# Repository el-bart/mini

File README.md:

mini
====

repo for mini-projects (one-filers, etc...).

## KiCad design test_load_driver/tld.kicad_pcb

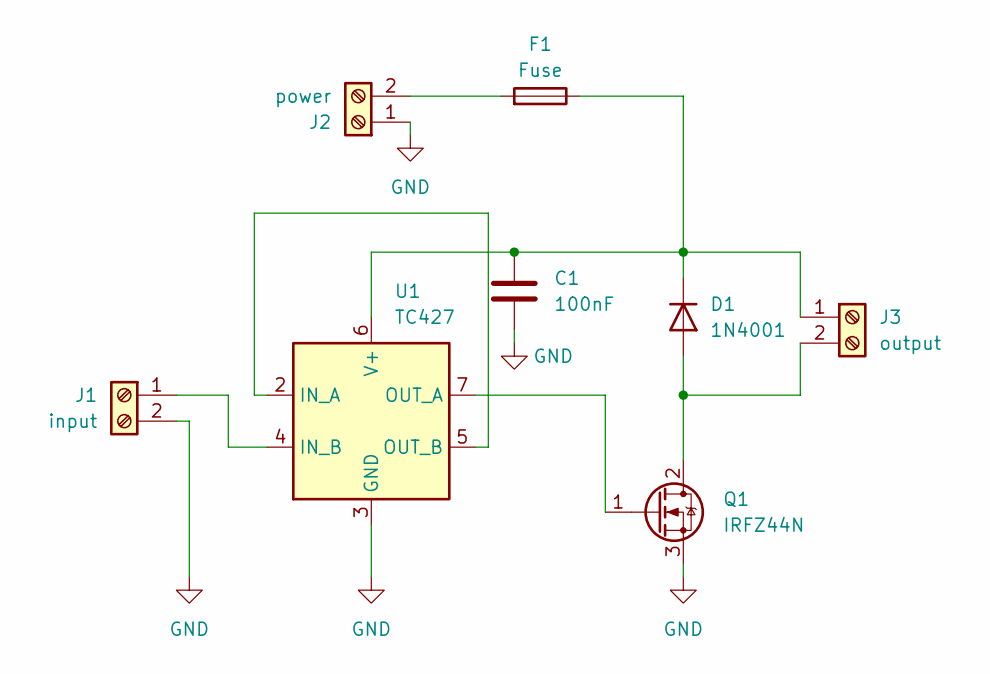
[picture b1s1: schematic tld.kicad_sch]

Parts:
C1: 100nF; C_Rect_L9.0mm_W2.5mm_P7.50mm_MKT
D1: 1N4001; D_DO-41_SOD81_P10.16mm_Horizontal
F1: Fuse; Fuseholder_Cylinder-5x20mm_Schurter_0031_8201_Horizontal_Op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
J1: input; PinHeader_1x02_P2.54mm_Vertical
J2: power; PinHeader_1x02_P2.54mm_Vertical
J3: output; PinHeader_1x02_P2.54mm_Vertical
Q1: IRFZ44N; TO-220-3_Vertical
U1: TC427; DIP-8_W7.62mm

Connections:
GND: C1.2, J1.2, J2.1, Q1.3 (S), U1.3 (GND)
unnamed: D1.2 (A), J3.2, Q1.2 (D)
unnamed: C1.1, D1.1 (K), F1.1, J3.1, U1.6 (V+)
unnamed: J1.1, U1.4 (IN_B)
unnamed: F1.2, J2.2
unnamed: Q1.1 (G), U1.7 (OUT_A)
unnamed: U1.2 (IN_A), U1.5 (OUT_B)

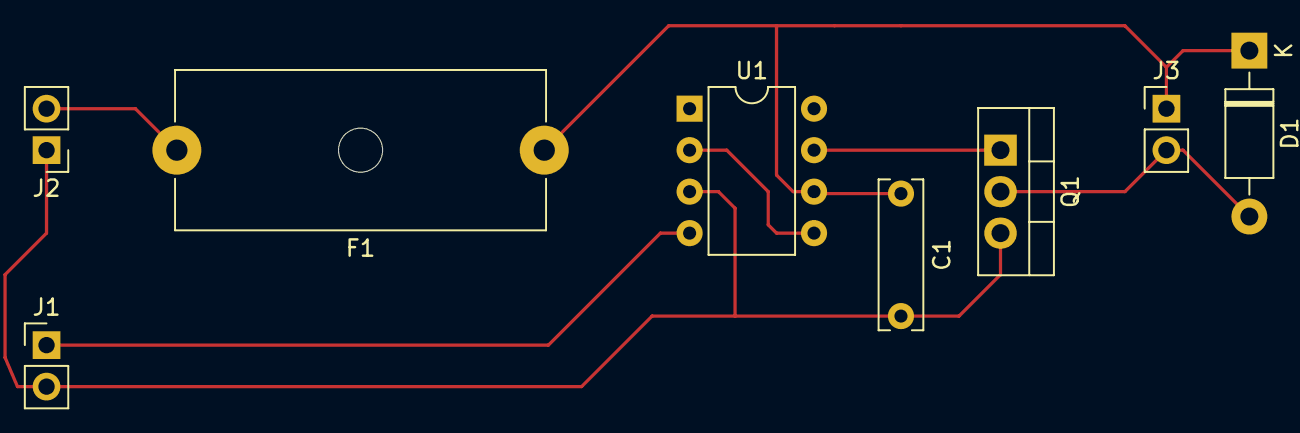
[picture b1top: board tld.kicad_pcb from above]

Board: 2 copper layers, 8 parts (0 on the bottom side), 7 nets.

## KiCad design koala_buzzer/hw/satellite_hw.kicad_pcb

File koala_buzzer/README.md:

# koala buzzer

fix board for child toy.
a buzzer, that lost controller board.

this uses PCB and other elements from [toy satellite model](https://github.com/el-bart/toy_satellite_model) project.
SW undergo minimal changes.

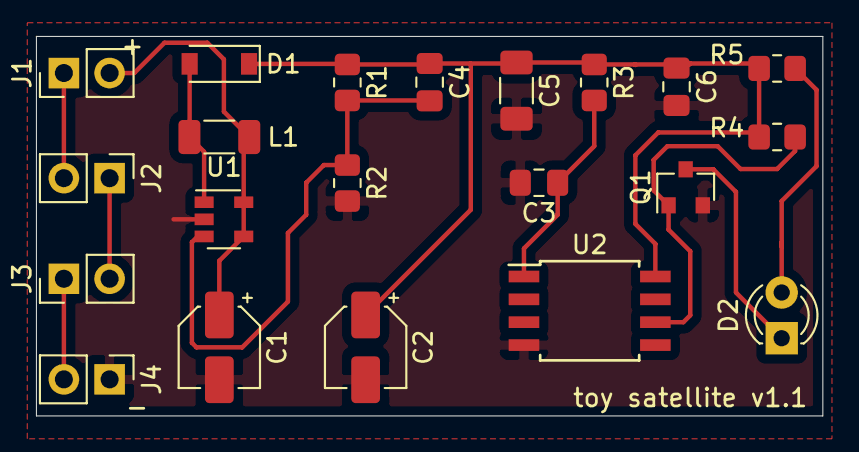
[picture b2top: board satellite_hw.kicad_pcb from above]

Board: 2 copper layers, 43.7 x 21.1 mm, 21 parts (0 on the bottom side), 12 nets.

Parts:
C1: 10µF; CP_Elec_4x3.9
C2: 1µF; CP_Elec_4x3.9
C3: 4.7nF; C_0805_2012Metric_Pad1.18x1.45mm_HandSolder
C4: 10pF; C_0805_2012Metric_Pad1.18x1.45mm_HandSolder
C5: 100nF; C_1206_3216Metric_Pad1.33x1.80mm_HandSolder
C6: 10nF; C_0805_2012Metric_Pad1.18x1.45mm_HandSolder
D1: D_Schottky; D_SOD-123
D2: red; LED_D3.0mm
J1: solar 1; PinHeader_1x02_P2.54mm_Vertical
J2: solar 2; PinHeader_1x02_P2.54mm_Vertical
J3: solar 3; PinHeader_1x02_P2.54mm_Vertical
J4: solar 4; PinHeader_1x02_P2.54mm_Vertical
L1: 10µH; L_1206_3216Metric_Pad1.22x1.90mm_HandSolder
Q1: 2N7002; SOT-23
R1: 680k; R_0805_2012Metric_Pad1.20x1.40mm_HandSolder
R2: 220k; R_0805_2012Metric_Pad1.20x1.40mm_HandSolder
R3, R4: 10k; R_0805_2012Metric_Pad1.20x1.40mm_HandSolder
R5: 470R; R_0805_2012Metric_Pad1.20x1.40mm_HandSolder
U1: AP3015; SOT-23-5
U2: ATtiny13-20SU; SOIJ-8_5.3x5.3mm_P1.27mm

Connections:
+5V: C2.1, C4.1, C5.1, C6.1, D1.1, R1.1, R3.1, R4.1, R5.1, U2.8
GNDD: C1.2, C2.2, C3.2, C5.2, C6.2, J4.1, Q1.2, R2.2, U1.2, U2.4
unnamed: C3.1, R3.2, U2.1
unnamed: C4.2, R1.2, R2.1, U1.3
unnamed: D1.2, L1.2, U1.1
unnamed: D2.1, Q1.3
unnamed: D2.2, R5.2
unnamed: J1.1, J2.2
unnamed: J2.1, J3.2
unnamed: J3.1, J4.2
unnamed: Q1.1, R4.2, U2.6
VCC: C1.1, J1.2, L1.1, U1.4, U1.5

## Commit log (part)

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2025-12-07 LED simplified
2025-12-07 watchdog set yo 8s
2025-12-07 back to 120ms
2025-12-07 adjsutements after changing namespaces
2025-12-07 SwPWM draft
2025-12-07 PoC with 50% duty cycle
2025-12-07 removed unused param
2025-12-07 helper scritp for computing gamma-correction LUT for AVR
2025-12-07 added fade in and out to main
2025-12-07 fade in and out impl. for LED::State + some compile-time constants to play with
2025-12-07 renamed LUT generator + added nicer formatting
2025-12-07 added custom cycle for on/off-s
2025-12-07 cycles are now generated using rand()
2025-12-08 added code generation for LUT
2025-12-08 using generated code now
2025-12-08 added PRNG seeded based on EEPROM, to save some entropy
2025-12-08 keeping seed as unsigned to avoid flipping signed values
2025-12-09 there's s macro for wairing for write to complete
2025-12-09 added C++ compliant number to pointer conversion
2025-12-09 working read-write example
2025-12-09 compile / flash / read hex scripts
2025-12-09 * fixed PRNG state saving * removed test / PoC code for EEPROM from main()
2025-12-09 moved compile time constant to a place where it's actually used
2025-12-09 more cannonical init
2025-12-21 xmass light mounts on a balkony - 3D SDK
2025-12-21 project description
2025-12-21 PET-G/waterproof
2025-12-21 corner hook design
2025-12-21 printing 10x at a time
2025-12-21 moved corner-hook-specific param to the model file
2025-12-21 prototype for a balcony hook
2025-12-21 6x books
2025-12-21 added rim around for some extra stiffness
2025-12-21 removed bottom notch
2025-12-21 adjusted printing parameters for easier printing
2025-12-29 added description of the repo
2025-12-29 3D SDK for camera mount
2025-12-29 1st draft of the mount base
2025-12-29 adjusted sizes, and rotated to for print orientation
2025-12-29 0.3mm layer height, as we're mor interested in speat than precision here
2025-12-29 added camera holder itself
2025-12-29 added Wayland forwardinf for steam (WIP)
2025-12-29 added missing libs for Vulkan and Mesa
2025-12-29 * added wayland forwarding * added steam flags to run non-sandboxed CEF
2025-12-29 steam bumped to debian:13 + added missing tools for Vulkan
2025-12-29 3D SDK for multiple marker holders for whiteboard
2025-12-29 multi-marker holder
2025-12-29 added some nice touches to make print easier to handle
2025-12-29 bed temperature down to 60°C for PLA/Silk
2026-01-01 added Xwayland for image
2026-01-01 WIP for Wayland
2026-01-01 removed Wayland testing code
2026-01-01 Wayland note
2026-01-01 fixed comment
2026-01-10 3D SDK for digital hourglass
2026-01-10 trigger board enc for USB-C added as a helper model
2026-01-10 added hourglass box
2026-01-11 draft of CubicSDR
2026-01-11 WIP...
2026-01-11 fixed SDR device access
2026-01-11 fixed path to dockerfile, when not running from a local dir
2026-01-11 3D SDK for AVT's dusk sensor
2026-01-11 USB-C trigger board
2026-01-11 dusk switch box
2026-01-11 added LED support strip, to make connection more firm (yes, it's not part of the set, but it's how my kids use it - so there u have it... ;))
2026-01-12 3D SDK for toy rocket cone
2026-01-12 model of the nose cone
2026-01-12 print settings a bit more optimized for speed
2026-01-14 3D SDK for laptop holder for the desk
2026-01-14 PET-G/strength
2026-01-14 holder for a laptop, attached to a desk
2026-01-14 no infill plz
2026-01-14 rpitning 2 copies at a time
2026-01-14 ajudsted sizes for more strength
2026-01-18 dehydration pipe holder for A/C unit
2026-01-18 A/C dehydration pipe holder
2026-01-23 f-14 moved to ext, as this is where it belongs
2026-01-30 3D SDK for flowerpot for Grzybek
2026-01-30 flowerpot sourcer added
2026-01-30 renamed file
2026-01-30 flowerpot itself
2026-01-30 25% PCF for surface quality
2026-01-31 added 1 more hole in the center
2026-01-31 adjusted size of side-balls to finish print faster
2026-02-03 yt-dlp wrapper running inside docker
2026-02-03 yt-dlp-docker description
2026-02-03 * added checking of the checksum of the downloaded archive * moved version and hash to a variable at the top of the file
2026-02-03 constants are now marged as readonly
2026-02-03 added ffmpeg for merging A+V files
2026-02-11 copilot-cli wrapper for docker
2026-02-11 simplified script and mounting rules
2026-02-11 whitelisting less by default
2026-02-14 3D SDK
2026-02-14 print solid
2026-02-14 box for random PCB for kids
2026-02-15 toy barrel plug ending
2026-02-15 non-scarf seam
2026-02-15 addjusted sizings and speeds
2026-02-15 steam-xwayland added
2026-02-25 yt-dlp bumped to 2026.02.21
2026-02-25 crontab might not always set USER
2026-02-28 new GPG key from steam
2026-03-07 nower yt-dlp with nodejs for JS code
2026-03-08 data and installer dirs
2026-03-08 base image for gaming
2026-03-08 scripts for gaming
2026-03-08 preventing network access for the container
2026-03-08 KSP installer bacame a base for dockerized linux games
2026-03-08 passing all the params down the chain
2026-03-08 added missing flag to run cmd with args under xterm
2026-03-08 template ./play script to be customized to run a game of chice
2026-03-08 brief project description
2026-03-28 3D SDK for hairdryer hook
2026-03-28 PLA / strength
2026-03-28 hairdryer hook
2026-03-28 simpler infill for faster printing
2026-03-28 2 hooks per hairdryer
2026-03-28 3D SDK for toy coil
2026-03-28 toy coil cap
2026-03-29 3D SDK for toy 3D lock box
2026-03-29 3-digit lock box model
2026-04-05 toy_3_digit_lock_box moved to ext. 3D projects, where it belongs
2026-04-09 newer yt-dlp
2026-04-22 3D SDK for toy relay box light
2026-04-22 wrap around the toy relay box for light
2026-04-24 3D SDK for colorful vase
2026-04-24 Silk/vase
2026-04-24 3D SDK bugfix
2026-04-24 printing thicker layers
2026-04-24 rainbow silk vase model
2026-04-24 added more precise rendering, for improved quality
2026-04-24 1st layers are to be more precise
2026-04-24 3D SDK - more tunning
2026-04-25 SR-71 model stand - 3D SDK
2026-04-25 model's base, to be installed on the LCD
2026-04-25 printing all in PLA + model of the mount itself
2026-04-25 added a bit steeper mount, for better outlook
2026-04-25 SR-71 model link added to stand
2026-04-30 SDK for rp2040
2026-04-30 added example app
2026-04-30 rp2040 demo app
2026-04-30 servo handling class
2026-04-30 added missing PWM-enable
2026-04-30 removed dead code for pin init
2026-04-30 2x servo experiment
2026-04-30 added structure to move all servos in tandem
2026-04-30 added ADC helper
2026-04-30 integreated ADC-to-servo position loop
2026-05-10 night of snow - model base
2026-05-10 night of snow - base model added
2026-05-10 asimo robot print in place - 3D SDK
2026-05-10 asimo robot print in place - model
2026-05-14 3D SDK for bike flag holder
2026-05-16 added some extra space on top for the screw's head
2026-05-18 3D SDK for enclosure for joystick
2026-05-18 back to PLA
2026-05-18 electronics box
2026-05-18 removed object highlighting
2026-05-28 game: KSP linux startup env
2026-05-28 game: TA linux startup env
2026-06-05 3D SDK for toy rocket shape
2026-06-05 body
2026-06-05 added cone part
2026-06-05 rocket is now a bit bigger and in 3 parts for faster print
2026-06-06 door knob's bistable block - 3D SDK
2026-06-06 3D SDK bump with TPU/solid profile
2026-06-06 TPU40D/solid
2026-06-06 project's description
2026-06-06 bistable door block - 1st draft
2026-06-06 thicker bounce + moved a bit lower to not interfere with top block
2026-06-06 generally avoid crossing perimeters for TPU, due to quality concerns
2026-06-06 going for higher layer height, to speed up the print
2026-06-06 label added to explain why larger layer lines
2026-06-06 new, triangle-based blocking corner approach + adjusted certain params
2026-06-06 replaced triangular shape with a simple hook
2026-06-06 slowed down a bit
2026-06-07 added booster to the print
2026-06-07 delfinki: thank you photo box - 3D SDK
2026-06-07 exterior - box's cover
2026-06-07 added nicer roundings
2026-06-07 added rough visualization of the bottom part
2026-06-07 top part of the box - WIP
2026-06-07 higher cut
2026-06-07 happy dolphin - vector graphics
2026-06-07 image slightly tweaked for better printing
2026-06-07 fixed SVG so that it forms a closed geometry
2026-06-07 added 'happy dolphin' engraving on the lid
2026-06-07 fixed box's h - the box_cut_edge_h is an overlap here
2026-06-08 printing in Silk/none + some quality-related modifications
2026-06-08 decreased amount of space for photos - turned out that the stack won't be that high
2026-06-08 added Z-cut for top and bottom layers
2026-06-08 added space for fingers, to be able to open the box conveniently
2026-06-08 added better positioning (in case of 2-in-1 printing)
2026-06-08 fingers cut-in depth adjusted
2026-06-08 added magnet slots on both sides
2026-06-08 added extra clearance on the top, to ensure box's lid won't wobble
2026-06-08 added explicit param to designate how deep the magnets should be burried
2026-06-09 added photodeck visualization
2026-06-09 added TODO for a future edition(s)
2026-06-10 dyzio wełniak - dir + readme
2026-06-10 dyzio wełniak - 3D SDK
2026-06-10 gabit
2026-06-10 3D SDK bump
2026-06-16 updated yt-dlp
2026-06-20 toy money box
2026-06-20 body of the main box
2026-06-20 main box is ready
2026-06-20 * added cover part * decreased height of the model
2026-06-20 * thicker wall * wider
2026-06-21 3D SDK for cooling duct adapter
2026-06-21 fan ring - test adapter / print
2026-06-21 renamed vars for fan_*
2026-06-21 added test duct print part
2026-06-21 for pipe-adapter we have fixed ext-diameter
2026-06-21 improved printing characteristics
2026-06-21 full funnel / adapter part
2026-06-21 0.3mm layer height for laster printing
2026-06-21 1st layer 0.3mm as well
2026-06-21 draft of the adapter holder tooth
2026-06-21 4 units at a time
2026-06-30 3D SDK for USB snd card holder
2026-06-30 USB card holder with 5x5mm cylindrical magnets
2026-06-30 project info
2026-06-30 * added air vent hole for magnet insertion * fixed wing size * decreased spacing for a tighter fit
